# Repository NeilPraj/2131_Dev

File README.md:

# 2131_Dev
Development board for the SSI2131

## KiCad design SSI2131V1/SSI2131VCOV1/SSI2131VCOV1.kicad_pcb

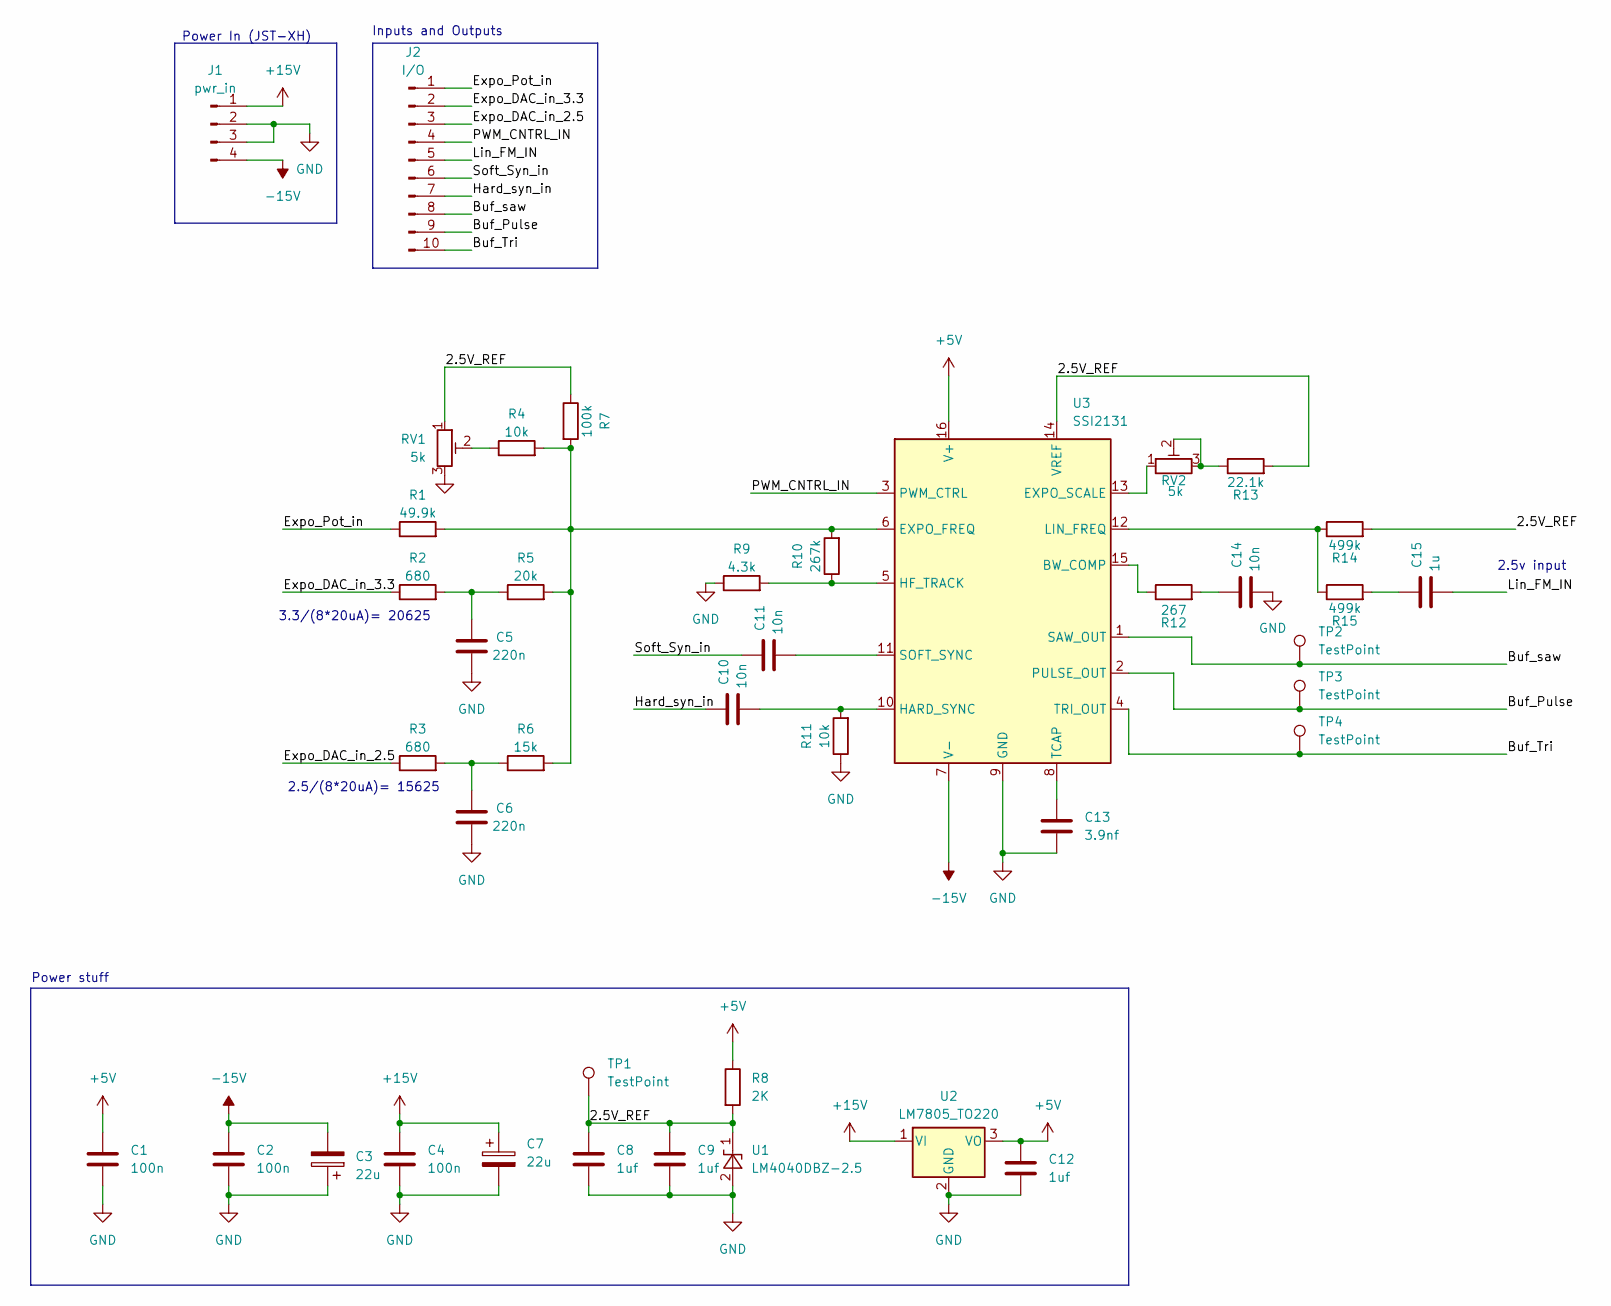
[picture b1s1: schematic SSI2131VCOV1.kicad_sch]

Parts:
C1: 100n; C_0805_2012Metric
C2, C4: 100n; C_0805_2012Metric_Pad1.18x1.45mm_HandSolder
C3, C7: 22u; CP_Elec_6.3x5.4
C5, C6: 220n; C_0805_2012Metric_Pad1.18x1.45mm_HandSolder
C8, C9, C12: 1uf; C_0805_2012Metric_Pad1.18x1.45mm_HandSolder
C10, C11, C14: 10n; C_0805_2012Metric_Pad1.18x1.45mm_HandSolder
C13: 3.9nf; C_0805_2012Metric_Pad1.18x1.45mm_HandSolder
C15: 1u; C_0805_2012Metric_Pad1.18x1.45mm_HandSolder
J1: pwr_in; JST_XH_B4B-XH-AM_1x04_P2.50mm_Vertical
J2: I/O; PinSocket_1x10_P2.54mm_Vertical
R1: 49.9k; R_0805_2012Metric_Pad1.20x1.40mm_HandSolder
R2, R3: 680; R_0805_2012Metric_Pad1.20x1.40mm_HandSolder
R4, R11: 10k; R_0805_2012Metric_Pad1.20x1.40mm_HandSolder
R5: 20k; R_0805_2012Metric_Pad1.20x1.40mm_HandSolder
R6: 15k; R_0805_2012Metric_Pad1.20x1.40mm_HandSolder
R7: 100k; R_0805_2012Metric_Pad1.20x1.40mm_HandSolder
R8: 2K; R_0805_2012Metric_Pad1.20x1.40mm_HandSolder
R9: 4.3k; R_0805_2012Metric_Pad1.20x1.40mm_HandSolder
R10: 267k; R_0805_2012Metric_Pad1.20x1.40mm_HandSolder
R12: 267; R_0805_2012Metric_Pad1.20x1.40mm_HandSolder
R13: 22.1k; R_0805_2012Metric_Pad1.20x1.40mm_HandSolder
R14, R15: 499k; R_0805_2012Metric_Pad1.20x1.40mm_HandSolder
RV1, RV2: 5k; Potentiometer_Bourns_3296W_Vertical
TP1, TP2, TP3, TP4: TestPoint; TestPoint_Pad_1.5x1.5mm
U1: LM4040DBZ-2.5; SOT-23
U2: LM7805_TO220; TO-220-3_Vertical
U3: SSI2131; SOP-16_3.9x9.9mm_P1.27mm

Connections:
+5V: C1.1, C12.1, R8.1, U2.3 (VO), U3.16 (V+)
+15V: C4.1, C7.1, J1.1, U2.1 (VI)
-15V: C2.1, C3.2, J1.4, U3.7 (V-)
/2.5V_REF: C8.1, C9.1, R7.1, R8.2, R13.2, R14.2, RV1.1, TP1.1, U1.1 (K), U3.14 (VREF)
/Buf_Pulse: J2.9, TP3.1, U3.2 (PULSE_OUT)
/Buf_Tri: J2.10, TP4.1, U3.4 (TRI_OUT)
/Buf_saw: J2.8, TP2.1, U3.1 (SAW_OUT)
/Expo_DAC_in_2.5: J2.3, R3.1
/Expo_DAC_in_3.3: J2.2, R2.1
/Expo_Pot_in: J2.1, R1.1
/Hard_syn_in: C10.1, J2.7
/Lin_FM_IN: C15.2, J2.5
/PWM_CNTRL_IN: J2.4, U3.3 (PWM_CTRL)
/Soft_Syn_in: C11.1, J2.6
GND: C1.2, C2.2, C3.1, C4.2, C5.2, C6.2, C7.2, C8.2, C9.2, C12.2, C13.2, C14.2, J1.2, J1.3, R9.1, R11.1, RV1.3, U1.2 (A), U2.2 (GND), U3.9 (GND)
unnamed: C5.1, R2.2, R5.1
unnamed: C6.1, R3.2, R6.1
unnamed: C14.1, R12.2
unnamed: C15.1, R15.2
unnamed: R4.1, RV1.2
unnamed: R13.1, RV2.2, RV2.3
unnamed: R12.1, U3.15 (BW_COMP)
unnamed: R1.2, R4.2, R5.2, R6.2, R7.2, R10.2, U3.6 (EXPO_FREQ)
unnamed: RV2.1, U3.13 (EXPO_SCALE)
unnamed: C10.2, R11.2, U3.10 (HARD_SYNC)
unnamed: R9.2, R10.1, U3.5 (HF_TRACK)
unnamed: R14.1, R15.1, U3.12 (LIN_FREQ)
unnamed: C11.2, U3.11 (SOFT_SYNC)
unnamed: C13.1, U3.8 (TCAP)

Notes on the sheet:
3.3/(8*20uA)= 20625
2.5/(8*20uA)= 15625
2.5v input
Power In (JST-XH)
Inputs and Outputs
Power stuff

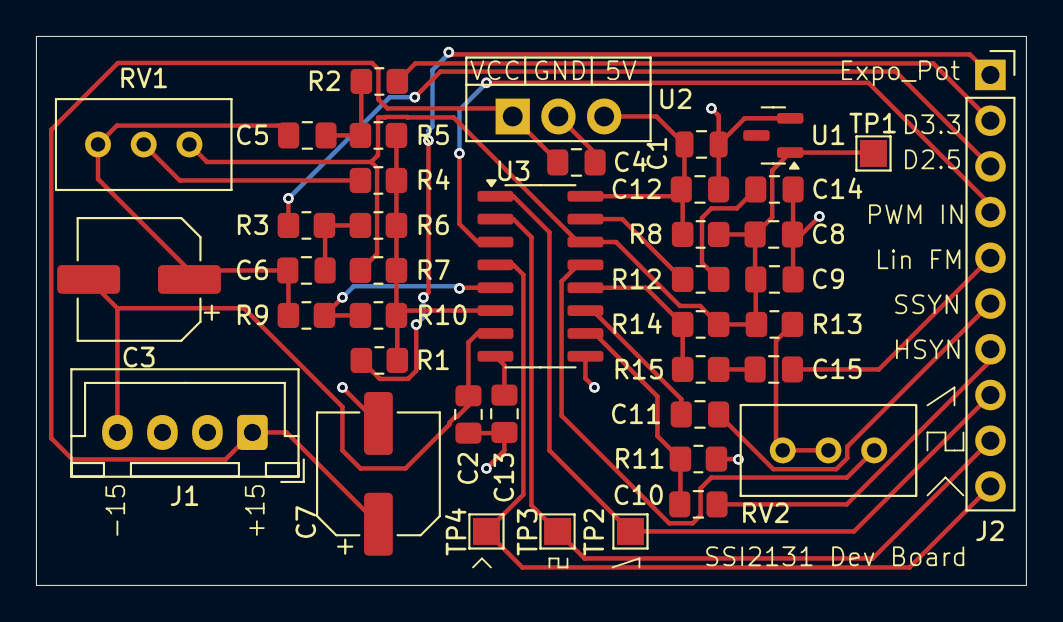
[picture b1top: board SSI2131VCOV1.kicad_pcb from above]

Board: 2 copper layers, 55.0 x 30.5 mm, 41 parts (0 on the bottom side), 29 nets.

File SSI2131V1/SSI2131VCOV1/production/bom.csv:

Designator,Footprint,Quantity,Value,LCSC Part #
"C1, C2, C4",0805,3,100n,
"C10, C11, C14",0805,3,10n,
"C12, C8, C9",0805,3,1uf,
C13,0805,1,3.9nf,
C15,0805,1,1u,
"C3, C7",CP_Elec_6.3x5.4,2,22u,
"C5, C6",0805,2,220n,
J1,JST_XH_B4B-XH-A_1x04_P2.50mm_Vertical,1,pwr_in,
J2,PinSocket_1x10_P2.54mm_Vertical,1,I/O,
R1,0805,1,49.9k,
R10,0805,1,267k,
"R11, R4",0805,2,10k,
R12,0805,1,267,
R13,0805,1,22.1k,
"R14, R15",0805,2,499k,
"R2, R3",0805,2,680,
R5,0805,1,20k,
R6,0805,1,15k,
R7,0805,1,100k,
R8,0805,1,2K,
R9,0805,1,4.3k,
"RV1, RV2",Potentiometer_Bourns_3296W_Vertical,2,5k,
"TP1, TP2, TP3, TP4",TestPoint_Pad_1.5x1.5mm,4,TestPoint,
U1,SOT-23,1,LM4040DBZ-2.5,
U2,TO-220-3_Vertical,1,LM7805_TO220,
U3,SOP-16_3.9x9.9mm_P1.27mm,1,SSI2131,
